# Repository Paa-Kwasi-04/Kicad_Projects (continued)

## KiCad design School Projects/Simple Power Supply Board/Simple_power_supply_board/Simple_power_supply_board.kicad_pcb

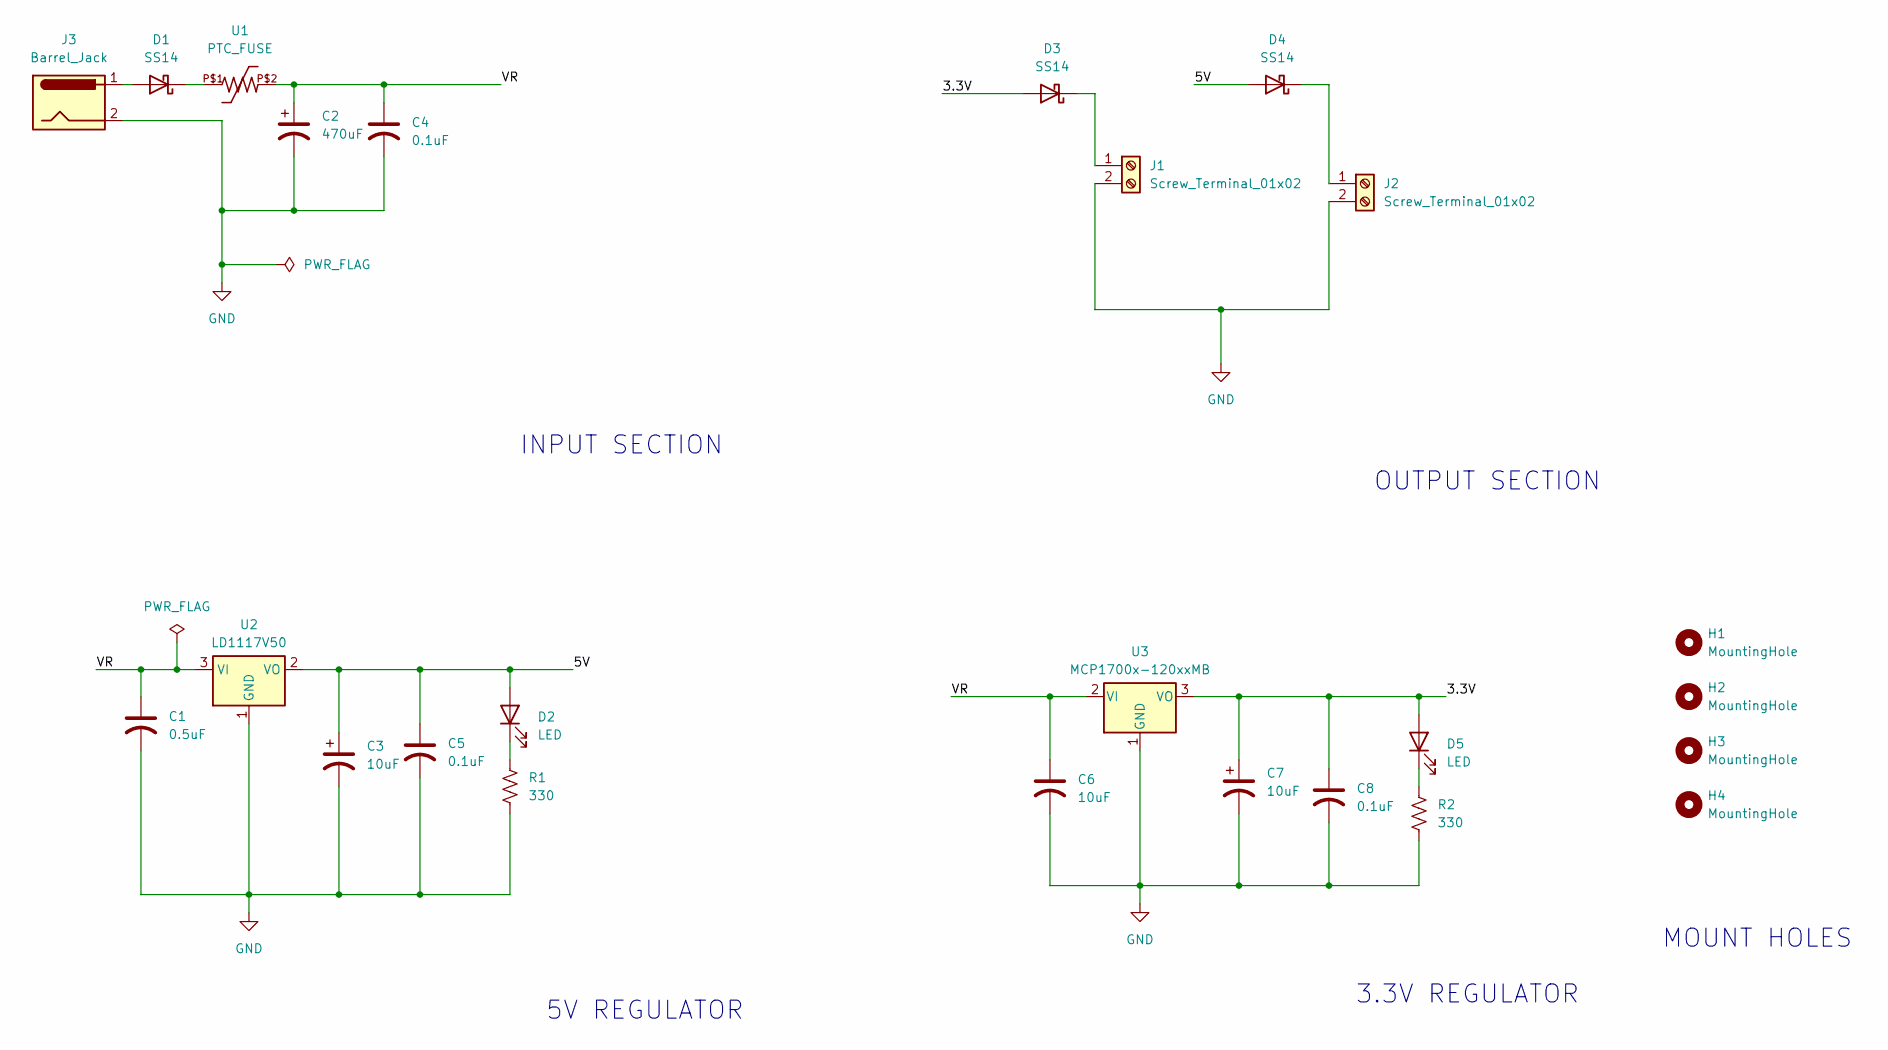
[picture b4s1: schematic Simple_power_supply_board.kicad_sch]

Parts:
C1: 0.5uF; CP_Axial_L10.0mm_D4.5mm_P15.00mm_Horizontal
C2: 470uF; CP_Axial_L10.0mm_D4.5mm_P15.00mm_Horizontal
C3, C6, C7: 10uF; CP_Axial_L10.0mm_D4.5mm_P15.00mm_Horizontal
C4, C5, C8: 0.1uF; CP_Axial_L10.0mm_D4.5mm_P15.00mm_Horizontal
D1, D3, D4: SS14; D_SMA
D2, D5: LED; LED_D3.0mm
H1, H2, H3, H4: MountingHole; MountingHole_2.2mm_M2_DIN965_Pad_TopOnly
J1, J2: Screw_Terminal_01x02; TerminalBlock_Phoenix_MKDS-1,5-2-5.08_1x02_P5.08mm_Horizont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
J3: Barrel_Jack; BarrelJack_GCT_DCJ200-10-A_Horizontal
R1, R2: 330; R_Axial_DIN0309_L9.0mm_D3.2mm_P12.70mm_Horizontal
U1: PTC_FUSE
U2: LD1117V50; TO-220-3_Vertical
U3: MCP1700x-120xxMB; SOT-89-3

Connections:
/3.3V: C7.1, C8.1, D3.2 (A), D5.2 (A), U3.3 (VO)
/5V: C3.1, C5.1, D2.2 (A), D4.2 (A), U2.2 (VO)
/VR: C1.1, C2.1, C4.1, C6.1, U1.P$2, U2.3 (VI), U3.2 (VI)
GND: C1.2, C2.2, C3.2, C4.2, C5.2, C6.2, C7.2, C8.2, J1.2, J2.2, J3.2, R1.2, R2.2, U2.1 (GND), U3.1 (GND)
unnamed: D1.2 (A), J3.1
unnamed: D1.1 (K), U1.P$1
unnamed: D2.1 (K), R1.1
unnamed: D3.1 (K), J1.1
unnamed: D4.1 (K), J2.1
unnamed: D5.1 (K), R2.1

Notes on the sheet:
OUTPUT SECTION
3.3V REGULATOR
MOUNT HOLES
5V REGULATOR
INPUT SECTION

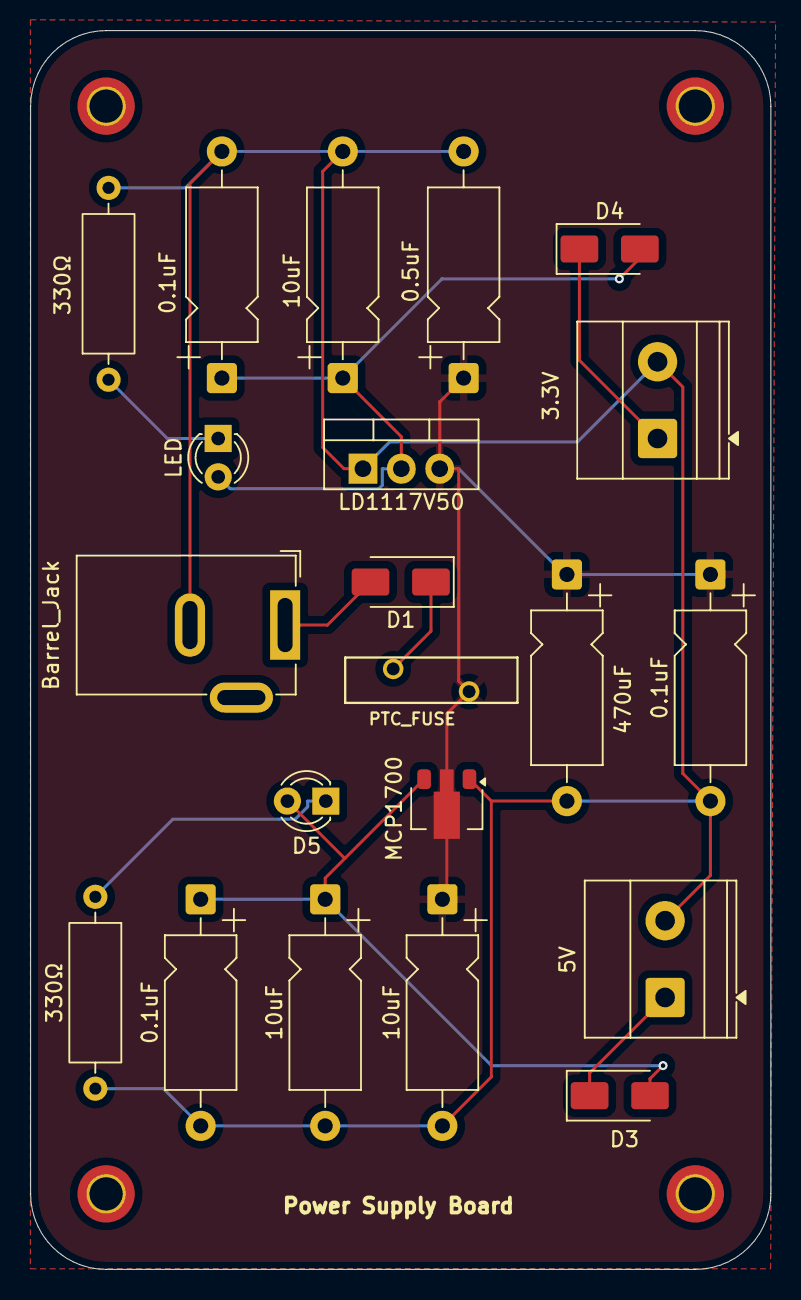
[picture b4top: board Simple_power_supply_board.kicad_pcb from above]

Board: 2 copper layers, 49.0 x 82.0 mm, 25 parts (0 on the bottom side), 10 nets.

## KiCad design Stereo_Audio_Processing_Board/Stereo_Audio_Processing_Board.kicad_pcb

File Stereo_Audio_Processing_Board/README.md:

# Stereo Audio Processing Board

## Description
This is a stereo audio processing circuit board designed for processing and amplifying stereo audio signals. The board can be used for audio amplification, filtering, mixing, or other signal processing applications. It features left and right channel processing for stereo audio applications.

## Features
- Stereo audio signal processing
- Left and right channel support
- Audio amplification and/or filtering
- Suitable for audio projects and sound systems
- Clean PCB layout for low noise performance

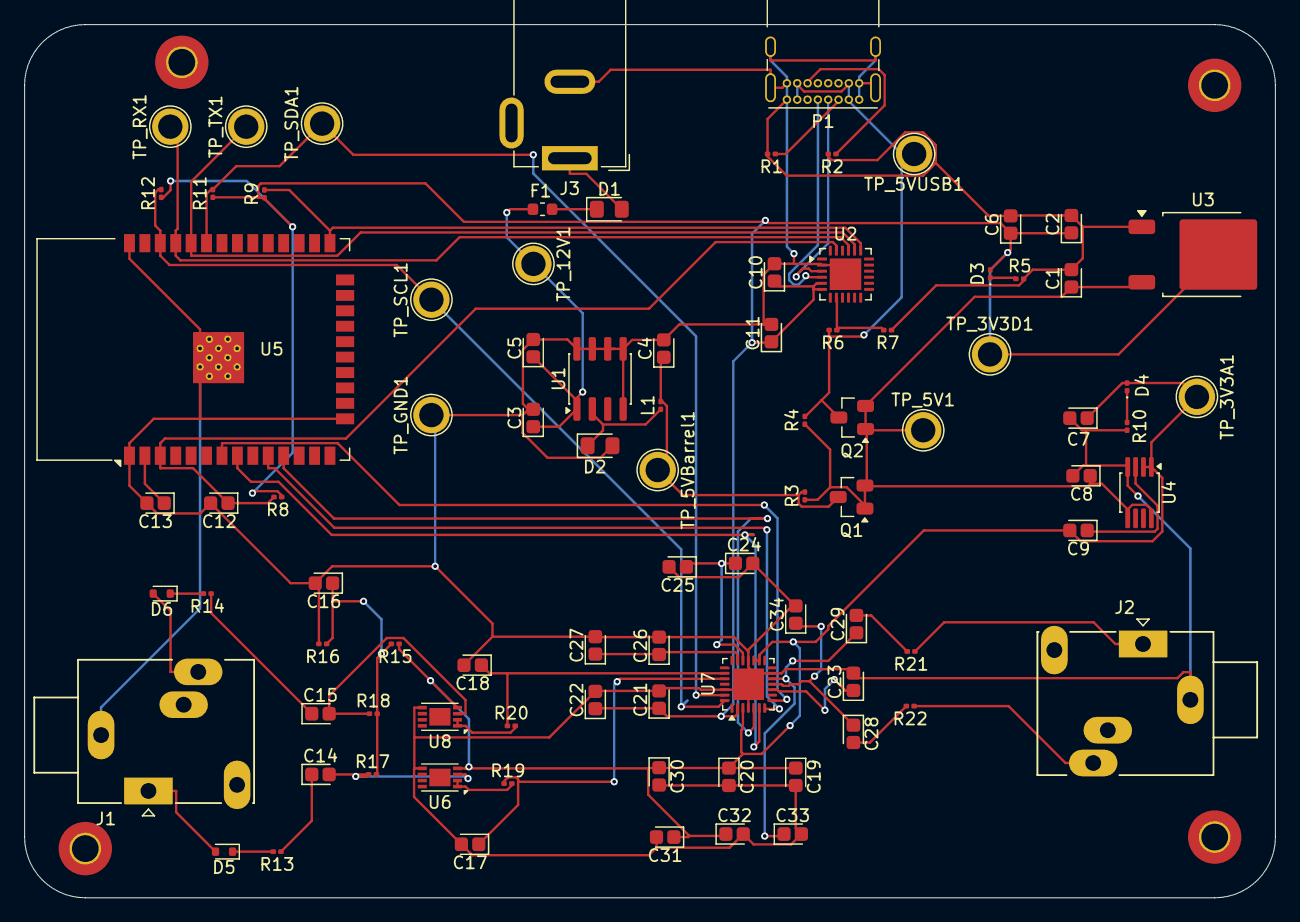
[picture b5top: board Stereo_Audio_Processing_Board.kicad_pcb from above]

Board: 2 copper layers, 103.0 x 71.9 mm, 93 parts (0 on the bottom side), 51 nets.

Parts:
C1, C2, C7, C14, C15, C16, C17, C18, C20, C21, C23, C24, C26, C30: 10uF; CP_EIA-1608-10_AVX-L
C3, C28, C29: 470uF; CP_EIA-1608-10_AVX-L
C4: 180uF; CP_EIA-1608-10_AVX-L
C5: 105F; CP_EIA-1608-10_AVX-L
C6, C8: 1uF; CP_EIA-1608-10_AVX-L
C9: 0.01uF; CP_EIA-1608-10_AVX-L
C10, C11, C13: 0.1µF; CP_EIA-1608-10_AVX-L
C12: 100nF; CP_EIA-1608-10_AVX-L
C19, C22, C25, C27, C31, C32, C33, C34: 0.1uF; CP_EIA-1608-10_AVX-L
D1: D_Schottky; D_0805_2012Metric_Pad1.15x1.40mm_HandSolder
D2: 1N5819WS; D_0805_2012Metric_Pad1.15x1.40mm_HandSolder
D3, D4: LED; LED_0201_0603Metric
D5, D6: ESD5Zxx; D_SOD-523
F1: Fuse; Fuse_0603_1608Metric
H1, H2, H3, H4: MountingHole; MountingHole_2.2mm_M2_Pad_TopBottom
J1, J2: AudioJack3; Jack_3.5mm_Ledino_KB3SPRS_Horizontal
J3: Barrel_Jack; BarrelJack_GCT_DCJ200-10-A_Horizontal
L1: 68uH; L_0201_0603Metric
P1: USB_C_Plug_USB2.0; USB_C_Receptacle_GCT_USB4085
Q1, Q2: PMOS; SuperSOT-3
R1, R2, R6: 5.1KΩ; R_0201_0603Metric
R3, R4, R15, R16: 100KΩ; R_0201_0603Metric
R5, R10: 330Ω; R_0201_0603Metric
R7, R8, R9, R11, R12, R13, R14, R19, R20: 10KΩ; R_0201_0603Metric
R17, R18: 1MΩ; R_0201_0603Metric
R21, R22: 33Ω; R_0201_0603Metric
TP_3V3A1: TestPoint_3V3A; TestPoint_Plated_Hole_D2.0mm
TP_3V3D1: TestPoint_3V3D; TestPoint_Plated_Hole_D2.0mm
TP_5V1: TestPoint_5V; TestPoint_Plated_Hole_D2.0mm
TP_5VBarrel1: TestPoint_5VBarrel; TestPoint_Plated_Hole_D2.0mm
TP_5VUSB1: TestPoint_5VUSB; TestPoint_Plated_Hole_D2.0mm
TP_12V1: TestPoint_12V; TestPoint_Plated_Hole_D2.0mm
TP_GND1: TestPoint_GND; TestPoint_Plated_Hole_D2.0mm
TP_RX1: TestPoint_RX; TestPoint_Plated_Hole_D2.0mm
TP_SCL1: TestPoint_SCL; TestPoint_Plated_Hole_D2.0mm
TP_SDA1: TestPoint_SDA; TestPoint_Plated_Hole_D2.0mm
TP_TX1: TestPoint_TX; TestPoint_Plated_Hole_D2.0mm
U1: XL1509-5.0; SOIC-8_3.9x4.9mm_P1.27mm
U2: CP2102N-Axx-xQFN24; QFN-24-1EP_4x4mm_P0.5mm_EP2.6x2.6mm
U3: NCP1117-3.3_TO252; TO-252-2
U4: LT1762-3.3; MSOP-8_3x3mm_P0.65mm
U5: ESP32-WROOM-32
U6, U8: MCP6002-xMC; DFN-8-1EP_3x2mm_P0.5mm_EP1.75x1.45mm
U7: ES8388; QFN-28-1EP_4x4mm_P0.45mm_EP2.6x2.6mm

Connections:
/3V3_ANA_POWER: C7.1, C9.2, C19.1, C20.1, C30.1, C31.1, C32.1, D4.2 (A), R15.1, TP_3V3A1.1, U4.1 (OUT), U4.2 (SENSE), U6.4 (V), U7.3 (PVDD), U7.16 (HPVDD), U7.17 (AVDD), U8.4 (V)
/3V3_DIG_POWER: C2.1, C6.1, C10.1, C11.1, C21.1, C22.1, D3.2 (A), R8.1, R9.1, R11.1, R12.1, TP_3V3D1.1, U2.5 (VIO), U2.6 (VDD), U3.2 (VO), U7.2 (DVDD)
/5V_POWER: C1.1, C8.1, Q1.1 (D), Q1.2 (G), Q2.1 (D), Q2.2 (G), R3.1, R4.1, TP_5V1.1, U3.3 (VI), U4.5 (~SHDN), U4.8 (IN)
/12V_POWER: C3.1, C5.1, F1.2, TP_12V1.1, U1.1 (VIN)
/ADCVREFF: C24.1, C25.1, U7.19 (ADCVREF)
/ASDOUT: U5.7 (IO35), U7.8 (ASDOUT)
/Barrel_POWER: C4.1, L1.2, Q1.3 (S), R3.2, TP_5VBarrel1.1
/D+: P1.A6 (D+), U2.3 (D+)
/D-: P1.A7 (D-), U2.4 (D-)
/DSDIN: U5.8 (IO32), U7.6 (DSDIN)
/DTR_EN: C12.1, R8.2, U2.23 (~DTR), U5.3 (EN)
/HP_AMP_IN_L: J2.T, R21.1
/HP_AMP_IN_R: J2.R, R22.1
/LBiased: C14.2, R17.1, U6.3 (+)
/LOUT1: C29.1, C33.1, U7.12 (LOUT1)
/LRCK: U5.10 (IO25), U7.7 (LRCK)
/L_AC_IN: C14.1, R13.1
/L_ADC_IN: C17.1, R19.1, U7.24 (LIN1)
/L_BUF: R19.2, U6.1, U6.2 (-)
/RBiased: C15.2, R18.1, U8.3 (+)
/ROUT1: C28.1, C34.1, U7.11 (ROUT1)
/RTS_IO0: R9.2, U2.19 (~RTS), U5.25 (IO0)
/RX: TP_RX1.1, U2.21 (TXD), U5.35 (TXD0/IO1)
/R_AC_IN: C15.1, R14.1
/R_ADC_IN: C18.1, R20.1, U7.23 (RIN1)
/R_BUF: R20.2, U8.1, U8.2 (-)
/SCL: R12.2, TP_SCL1.1, U5.36 (IO22), U7.28 (CCLK)
/SCLK: U5.11 (IO26), U7.5 (SCLK)
/SDA: R11.2, TP_SDA1.1, U5.33 (IO21), U7.27 (CDATA)
/TX: TP_TX1.1, U2.20 (RXD), U5.34 (RXD0/IO3)
/USB_POWER: P1.A4 (VBUS), P1.A9 (VBUS), P1.B4 (VBUS), P1.B9 (VBUS), Q2.3 (S), R4.2, R6.2, TP_5VUSB1.1
/VBias: C16.1, R15.2, R16.1, R17.2, R18.2
/VMID: C26.1, C27.1, U7.20 (VMID)
/VREF: C23.1, U7.10 (VREF)
GND: C1.2, C2.2, C3.2, C4.2, C5.2, C6.2, C7.2, C8.2, C10.2, C11.2, C12.2, C13.2, C16.2, C17.2, C18.2, C19.2, C20.2, C21.2, C22.2, C23.2, C24.2, C25.2, C26.2, C27.2, C30.2, C31.2, C32.2, C33.2, C34.2, D2.2 (A), J1.S, J2.S, J3.2, P1.A1 (GND), P1.A12 (GND), P1.B1 (GND), P1.B12 (GND), P1.S1 (SHIELD), R1.2, R2.2, R5.2, R7.1, R10.2, R16.2, TP_GND1.1, U1.4 (~EN), U1.5 (GND), U1.6 (GND), U1.7 (GND), U1.8 (GND), U2.2 (GND), U2.25 (GND), U3.1 (GND), U4.4 (GND), U5.1 (GND), U5.15 (GND), U5.38 (GND), U5.39 (GND), U6.5 (G), U7.4 (DGND), U7.13 (HPGND), U7.18 (AGND), U7.26 (CE), U7.29 (EPAD), U8.5 (G)
unnamed: C28.2, R22.2
unnamed: C29.2, R21.2
unnamed: D1.2 (A), J3.1
unnamed: D1.1 (K), F1.1
unnamed: D2.1 (K), L1.1, U1.2 (OUT)
unnamed: D3.1 (K), R5.1
unnamed: D4.1 (K), R10.1
unnamed: D5.2 (A), J1.T
unnamed: D5.1 (K), R13.2
unnamed: D6.2 (A), J1.R
unnamed: D6.1 (K), R14.2
unnamed: P1.A5 (CC), R1.1
unnamed: P1.B5 (VCONN), R2.1
unnamed: R6.1, R7.2, U2.8 (VBUS)
unnamed: C9.1, U4.3 (BYP)
unnamed: C13.1, U5.2 (VDD)
